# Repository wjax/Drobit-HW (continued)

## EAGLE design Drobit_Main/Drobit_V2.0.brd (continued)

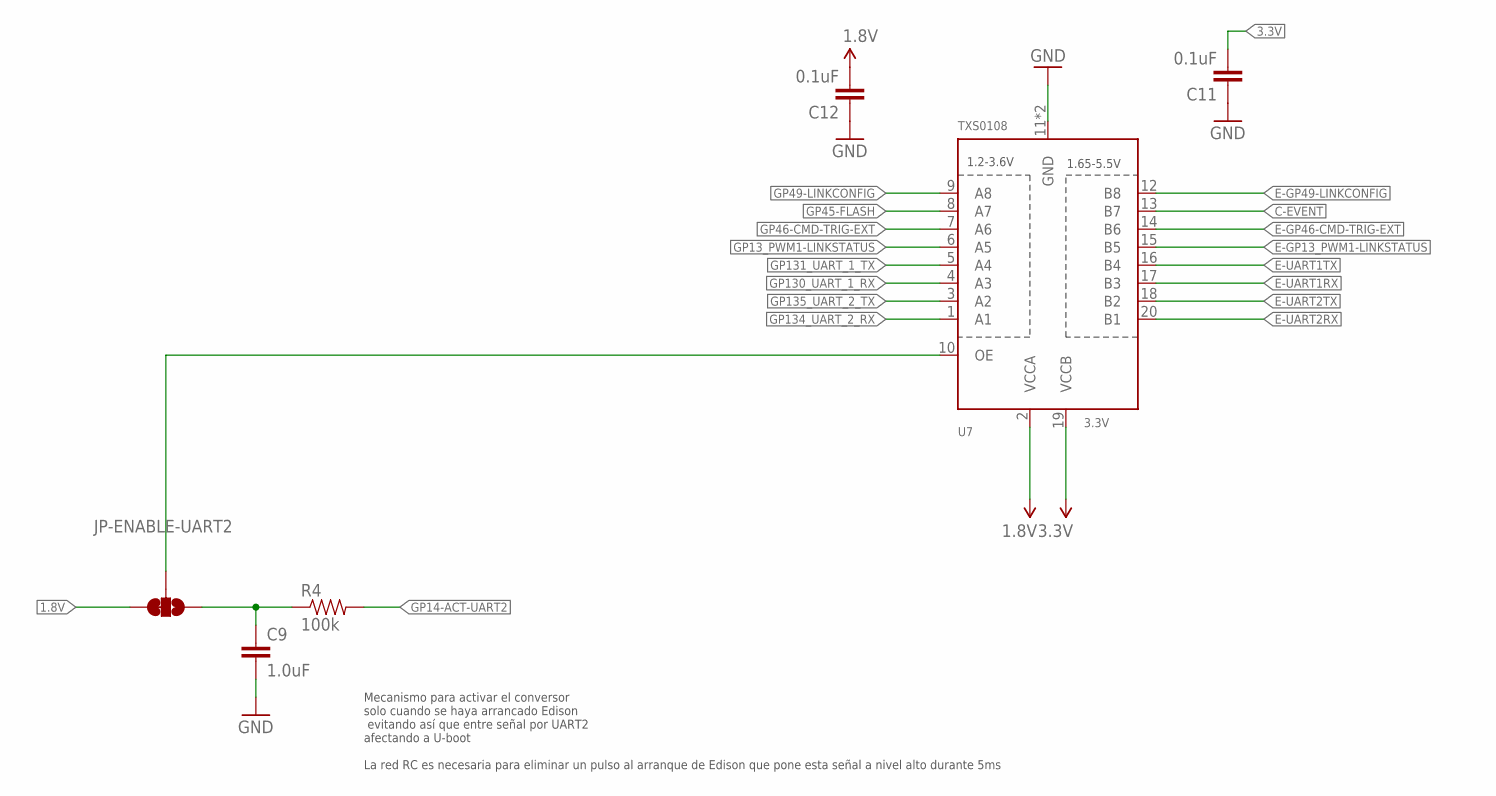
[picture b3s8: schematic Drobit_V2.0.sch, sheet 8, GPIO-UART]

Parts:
C9: 1.0uF; 0603-CAP; PARTNO 810-CGA3E1X7R1E105K
C11, C12: 0.1uF; 0603-CAP; PARTNO 810-CGA3E2X7R1E104K
JP-ENABLE-UART2: JUMPER-PAD-3-2OF3_NC_BY_TRACE_SMALL; PAD-JUMPER-3-2OF3_NC_BY_TRACE_YES_SILK_FULL_BOX
R4: 100k; 0603-RES; PARTNO 594-MCT06030C1003FP5
U7: TXS0108; R-PVQFN-N20; PARTNO 595-TXS0108ERGYR

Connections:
1.8V: C12.2, JP-ENABLE-UART2.3, U7.2 (VCCA); also elsewhere on the board
3.3V: C11.2, U7.19 (VCCB); also elsewhere on the board
C-EVENT: U7.13 (B7); also elsewhere on the board
E-GP13_PWM1-LINKSTATUS: U7.15 (B5); also elsewhere on the board
E-GP46-CMD-TRIG-EXT: U7.14 (B6); also elsewhere on the board
E-GP49-LINKCONFIG: U7.12 (B8); also elsewhere on the board
E-UART1RX: U7.17 (B3); also elsewhere on the board
E-UART1TX: U7.16 (B4); also elsewhere on the board
E-UART2RX: U7.20 (B1); also elsewhere on the board
E-UART2TX: U7.18 (B2); also elsewhere on the board
GND: C9.2, C11.1, C12.1, U7.11 (GND), U7.EPAD (GND); also elsewhere on the board
GP13_PWM1-LINKSTATUS: U7.6 (A5); also elsewhere on the board
GP14: JP-ENABLE-UART2.2, U7.10 (OE)
GP14-ACT-UART2: R4.2; also elsewhere on the board
GP45-FLASH: U7.8 (A7); also elsewhere on the board
GP46-CMD-TRIG-EXT: U7.7 (A6); also elsewhere on the board
GP49-LINKCONFIG: U7.9 (A8); also elsewhere on the board
GP130_UART_1_RX: U7.4 (A3); also elsewhere on the board
GP131_UART_1_TX: U7.5 (A4); also elsewhere on the board
GP134_UART_2_RX: U7.1 (A1); also elsewhere on the board
GP135_UART_2_TX: U7.3 (A2); also elsewhere on the board
unnamed: C9.1, JP-ENABLE-UART2.1, R4.1

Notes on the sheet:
Mecanismo para activar el conversor solo cuando se haya arrancado Edison evitando así que entre señal por UART2 afectando a U-boot La red RC es necesaria para eliminar un pulso al arranque de Edison que pone esta señal a nivel alto durante 5ms

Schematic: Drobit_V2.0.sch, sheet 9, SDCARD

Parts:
C7, C13: 0.1uF; 0603-CAP; PARTNO 810-CGA3E2X7R1E104K
SD: SDCARD; 1040310811; PARTNO 538-104031-0811
U9: TXS0108; R-PVQFN-N20; PARTNO 595-TXS0108ERGYR

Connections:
1.8V: C7.1, U9.2 (VCCA), U9.10 (OE); also elsewhere on the board
3.3V: C13.1, SD.D4, U9.19 (VCCB); also elsewhere on the board
E-GP182_PWM2-PPS: U9.12 (B8); also elsewhere on the board
GND: C7.2, C13.2, SD.CD2, SD.D6, SD.GND, SD.GND1 (GND), SD.GND2 (GND), SD.GND3 (GND), U9.11 (GND), U9.EPAD (GND); also elsewhere on the board
GP77_SD_0_CD#: SD.CD1; also elsewhere on the board
GP78_SD_0_CLK: U9.5 (A4); also elsewhere on the board
GP79_SD_0_CMD: U9.4 (A3); also elsewhere on the board
GP80_SD_0_DAT0: U9.6 (A5); also elsewhere on the board
GP81_SD_0_DAT1: U9.7 (A6); also elsewhere on the board
GP82_SD_0_DAT2: U9.1 (A1); also elsewhere on the board
GP83_SD_0_DAT3: U9.3 (A2); also elsewhere on the board
GP84_SD_CLK_FB: U9.8 (A7); also elsewhere on the board
GP182_PWM2-PPS: U9.9 (A8); also elsewhere on the board
unnamed: SD.D1, U9.20 (B1)
unnamed: SD.D2, U9.18 (B2)
unnamed: SD.D3, U9.17 (B3)
unnamed: SD.D7, U9.15 (B5)
unnamed: SD.D8, U9.14 (B6)
SCK: SD.D5, U9.13 (B7), U9.16 (B4)

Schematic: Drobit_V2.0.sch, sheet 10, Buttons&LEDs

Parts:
D-ON: ROJO - APT1608SECK/J3-PRV; LED-0603; PARTNO 604-APT1608SECKJ3PRV
D-REC: ORANGE - APT1608SECK/J4-PRV; LED-0603; PARTNO 604-APT1608SECKJ4PRV
D-SAT: VERDE - APT1608ZGCK; LED-0603; PARTNO 604-APT1608ZGCK
D-TRIGGER: BLUE - APT1608VBC/D; LED-0603; PARTNO 604-APT1608VBC/D
R3, R15: 10K; 0603-RES; PARTNO 667-ERJ-3EKF1002V
R19: 180; 0603-RES; PARTNO 667-ERJ-3GEYJ181V
R20, R24: 105; 0603-RES; PARTNO 667-ERJ-3EKF1050V
R28: 82; 0603-RES; PARTNO 667-ERJ-3EKF82R0V
SREC: SKRKAEE010; PARTNO 688-SKRKAE
T2, T3: BSS138PS; SOT363; PARTNO 771-BSS138BKS115

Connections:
1.8V: R15.1; also elsewhere on the board
3.3V: D-ON.A; also elsewhere on the board
5V: D-REC.A, D-SAT.A, D-TRIGGER.A; also elsewhere on the board
GND: R28.1, SREC.O, T2.1 (S), T2.4 (S), T3.1 (S); also elsewhere on the board
GP15-LEDSAT: T3.2 (G); also elsewhere on the board
GP44-STARTREC: R15.2, SREC.I; also elsewhere on the board
GP48-LEDTRIGIN: T2.5 (G); also elsewhere on the board
GP165-LEDREC: T2.2 (G); also elsewhere on the board
unnamed: D-ON.C, R28.2
PWRBTN#: R3.2; also elsewhere on the board
V_CH_SYS: R3.1; also elsewhere on the board
X-LEDREC: R19.2, T2.6 (D); also elsewhere on the board
X-LEDREC--: D-REC.C, R19.1
X-SAT: R24.2, T3.6 (D); also elsewhere on the board
X-SAT--: D-SAT.C, R24.1
X-TRIGGER: R20.2, T2.3 (D); also elsewhere on the board
X-TRIGGER--: D-TRIGGER.C, R20.1

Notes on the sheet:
Start Recording
Power button Edison
LED Recording ON/OFF
LED Trigger Event
Satellites (from COMNAV)

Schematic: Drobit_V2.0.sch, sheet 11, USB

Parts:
C22: 22UF; 0603-CAP; PARTNO 810-C1608X5R1A226M
R16: 287; 0603-RES; PARTNO 667-ERJ-3EKF2870V
R17: 10K; 0603-RES; PARTNO 667-ERJ-3EKF1002V
R18: 100k; 0603-RES; PARTNO 594-MCT06030C1003FP5
USB: 10103594-0001LF; POS-5; PARTNO 649-10103594-0001LF
USBREG: MIC2039; SOT23-6; PARTNO 998-MIC2039EYM6T5

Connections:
1.8V: R17.1; also elsewhere on the board
5V: USBREG.1 (VIN); also elsewhere on the board
FAULT: R17.2, USBREG.4 (!FAULT); also elsewhere on the board
GND: C22.2, R16.1, R18.1, USB.5 (GND), USB.PAD1 (GND), USB.PAD2 (GND), USB.PAD3 (GND), USB.PAD4 (GND), USB.PAD5 (GND), USB.PAD6 (GND), USBREG.2 (GND); also elsewhere on the board
unnamed: R16.2, USBREG.5 (ILIM)
PSW: R18.2, USBREG.3 (EN); also elsewhere on the board
USB_DN: USB.2 (D-); also elsewhere on the board
USB_DP: USB.3 (D+); also elsewhere on the board
USB_ID: USB.4 (ID); also elsewhere on the board
USB_VBUS: C22.1, USB.1 (VCC), USBREG.6 (VOUT); also elsewhere on the board

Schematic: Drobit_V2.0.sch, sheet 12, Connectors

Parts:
BATT: CONN_2-1-SFH; SM02B-SFHRS-TF; PARTNO 455-2524-1-ND
EXT-INTERFACE: M40-3100345R; PARTNO 855-M40-3100345R
PWR: JST_PH_G; JST-PH-2-SMT-RA; PARTNO 455-1749-1-ND
R61, R62: 10K; 0603-RES; PARTNO 667-ERJ-3EKF1002V
TRIG-IN: CONN_2-1; JST-GH-2; PARTNO 455-1564-1-ND
TRIG-OUT: CONN_7-1; JST-GH-7; PARTNO 455-1569-1-ND
TVS1, TVS2, TVS3, TVS4, TVS5, TVS6, TVS7, TVS8, TVS9, TVS10: LXES15AAA1-133; 1005; PARTNO 81-LXES15AAA1-133
UART-EXT: CONN_4-1; JST-GH-4; PARTNO 455-1566-1-ND

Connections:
1.8V: TRIG-OUT.6; also elsewhere on the board
3.3V: R61.2, R62.2; also elsewhere on the board
3.3V_LOCAL: TRIG-OUT.1; also elsewhere on the board
5VACC: EXT-INTERFACE.5, UART-EXT.1; also elsewhere on the board
C-EVENT: R61.1, TRIG-OUT.3; also elsewhere on the board
E-GP46-CMD-TRIG-EXT: R62.1, TRIG-IN.1, TVS10.1 (G); also elsewhere on the board
E-UART2RX: TVS2.1 (G), UART-EXT.2; also elsewhere on the board
E-UART2TX: TVS1.2 (IO), UART-EXT.3; also elsewhere on the board
GND: BATT.2, BATT.GND, BATT.GND1 (GND), EXT-INTERFACE.4, PWR.2, PWR.NC1 (3), PWR.NC2 (3), TRIG-IN.2, TRIG-IN.P1 (GND), TRIG-IN.P2 (GND), TRIG-OUT.7, TRIG-OUT.P1 (GND), TRIG-OUT.P2 (GND), TVS1.1 (G), TVS2.2 (IO), TVS3.2 (IO), TVS4.1 (G), TVS5.1 (G), TVS6.1 (G), TVS7.1 (G), TVS8.1 (G), TVS9.1 (G), TVS10.2 (IO), UART-EXT.4, UART-EXT.P1 (GND), UART-EXT.P2 (GND); also elsewhere on the board
GP12_PWM0_TRIG_OUT: TRIG-OUT.2, TVS3.1 (G); also elsewhere on the board
GP44-STARTREC: EXT-INTERFACE.1, TVS9.2 (IO); also elsewhere on the board
SCL_CAM: TRIG-OUT.4, TVS4.2 (IO); also elsewhere on the board
SDA_CAM: TRIG-OUT.5, TVS5.2 (IO); also elsewhere on the board
VCC_RAW_12V: PWR.1; also elsewhere on the board
V_CH_BAT: BATT.1; also elsewhere on the board
X-LEDREC: EXT-INTERFACE.2, TVS8.2 (IO); also elsewhere on the board
X-SAT: EXT-INTERFACE.6, TVS6.2 (IO); also elsewhere on the board
X-TRIGGER: EXT-INTERFACE.3, TVS7.2 (IO); also elsewhere on the board

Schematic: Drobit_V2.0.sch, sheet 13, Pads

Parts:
C-RX2: TPTP08R; TP08R
C-TX2: TPTP08R; TP08R
GP45, GP46: TPTP08R; TP08R
PPS: TPTP08R; TP08R

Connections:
C-COM2RX: C-RX2.TP; also elsewhere on the board
C-COM2TX: C-TX2.TP; also elsewhere on the board
C-EVENT: GP45.TP; also elsewhere on the board
E-GP46-CMD-TRIG-EXT: GP46.TP; also elsewhere on the board
E-GP182_PWM2-PPS: PPS.TP; also elsewhere on the board

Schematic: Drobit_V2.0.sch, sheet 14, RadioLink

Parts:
C14: 1.0uF; 0603-CAP; PARTNO 810-CGA3E1X7R1E105K
C15: 2.2uF; 0603-CAP; PARTNO 810-CGA3E1X5R1C225K
C16: 10nF; 0603-CAP; PARTNO 810-CGA3E2X7R1H103K
DC3VLINK: TPS73501DRBT; SON65P300X300X100-9N; PARTNO 595-TPS73501DRBR
JP_LINK: JUMPER-PAD-2-NOYES_SILK; PAD-JUMPER-2-NO_YES_SILK
LINK: HM-TRLR-S
X1: ANTENNA_U.FL-A-1JB; U.FL-A-1JB; PARTNO 523-A-1JB

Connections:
5VACC: C14.1, DC3VLINK.5 (EN), DC3VLINK.8 (IN); also elsewhere on the board
E-GP13_PWM1-LINKSTATUS: LINK.STATUS; also elsewhere on the board
E-GP49-LINKCONFIG: LINK.CONFIG; also elsewhere on the board
E-UART2RX: LINK.TXD; also elsewhere on the board
E-UART2TX: LINK.RXD; also elsewhere on the board
GND: C14.2, C15.2, C16.2, DC3VLINK.4 (GND), DC3VLINK.GND, DC3VLINK.GND1 (GND), DC3VLINK.GND2 (GND), DC3VLINK.GND3 (GND), DC3VLINK.GND4 (GND), LINK.GND, LINK.GND2 (GND1), LINK.SLEEP, X1.1 (GND), X1.2 (GND); also elsewhere on the board
unnamed: C16.1, DC3VLINK.3 (NR/FB)
unnamed: JP_LINK.2, LINK.RESET, LINK.VCC
unnamed: LINK.ANT, X1.3 (SIGNAL)
V3.3VLINK: C15.1, DC3VLINK.1 (OUT), JP_LINK.1

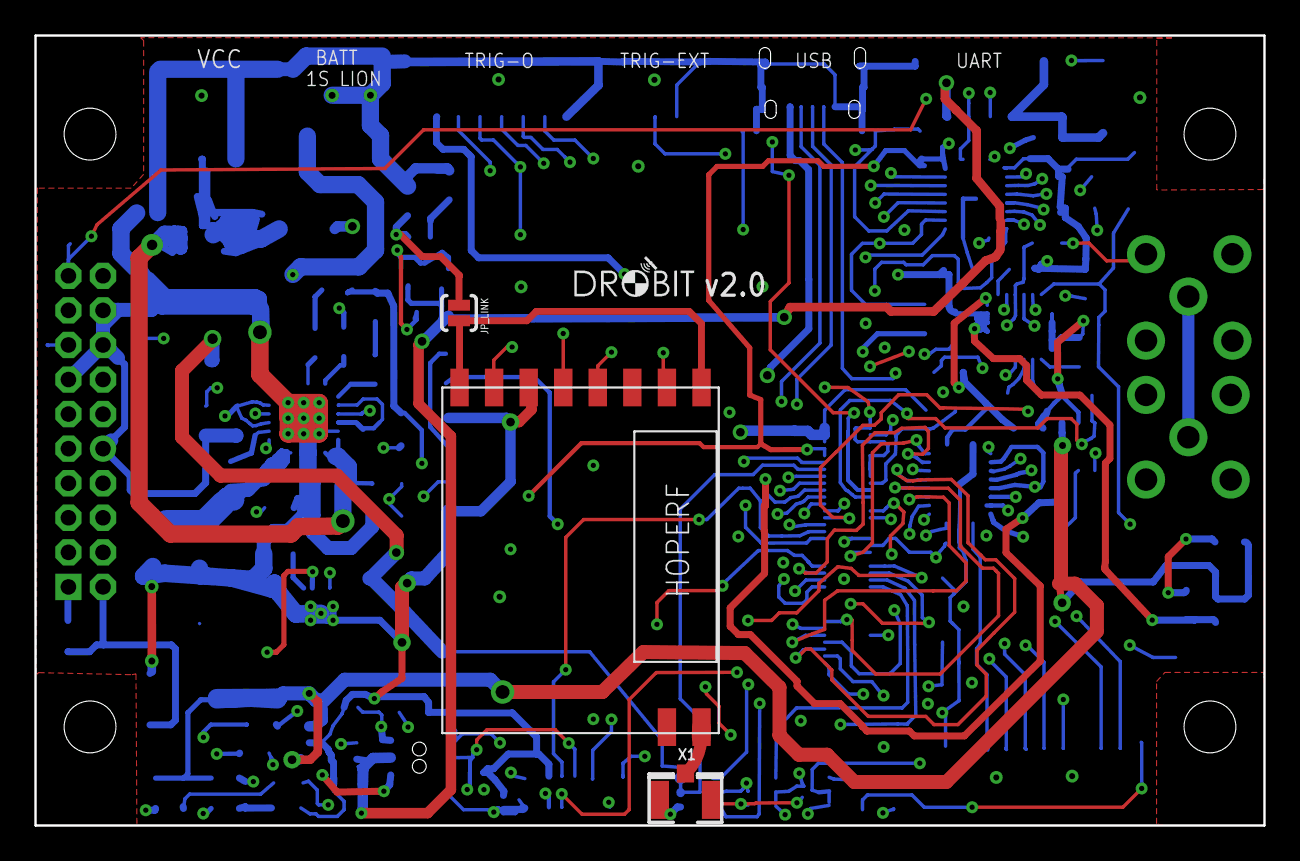
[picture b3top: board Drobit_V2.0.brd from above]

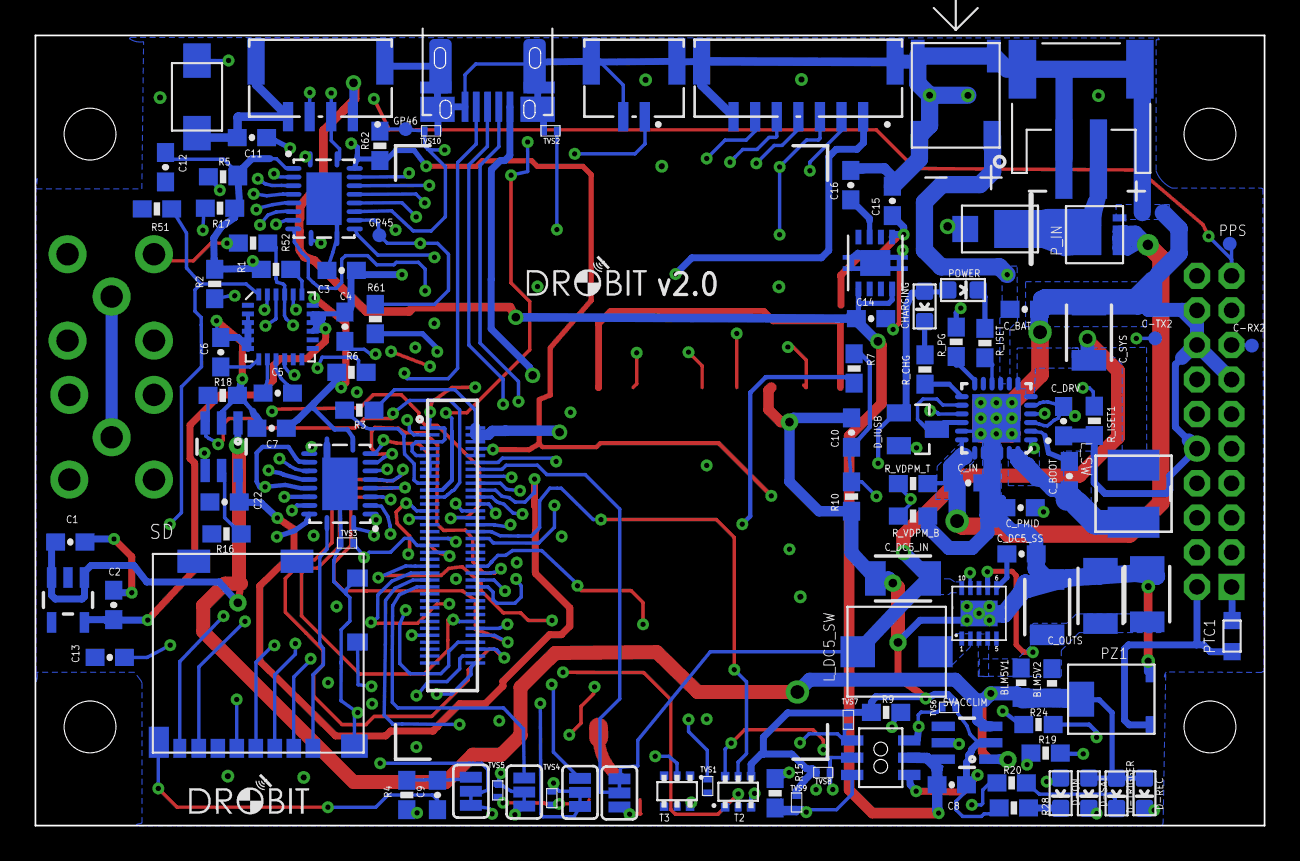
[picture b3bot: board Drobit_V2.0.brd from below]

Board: 4 copper layers, 71.1 x 45.7 mm, 115 parts (110 on the bottom side), 106 nets.
